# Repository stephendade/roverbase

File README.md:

# roverbase
A PCB design for Power and Motor control for small robots

This is a PCB design for a robot. It uses 4x 18650 batteries to provide a regulated power supply for electronics, power monitoring and 2x brushed motor controllers.

Todo:
Flip JST-GH power connector
5V power reg - put components closer together
Ext switch option for power switches (W/ESD protection?)
Put power power and power connectors further from battery case
Remove fuse. Look at current limiting FET?
Better alignment of labels

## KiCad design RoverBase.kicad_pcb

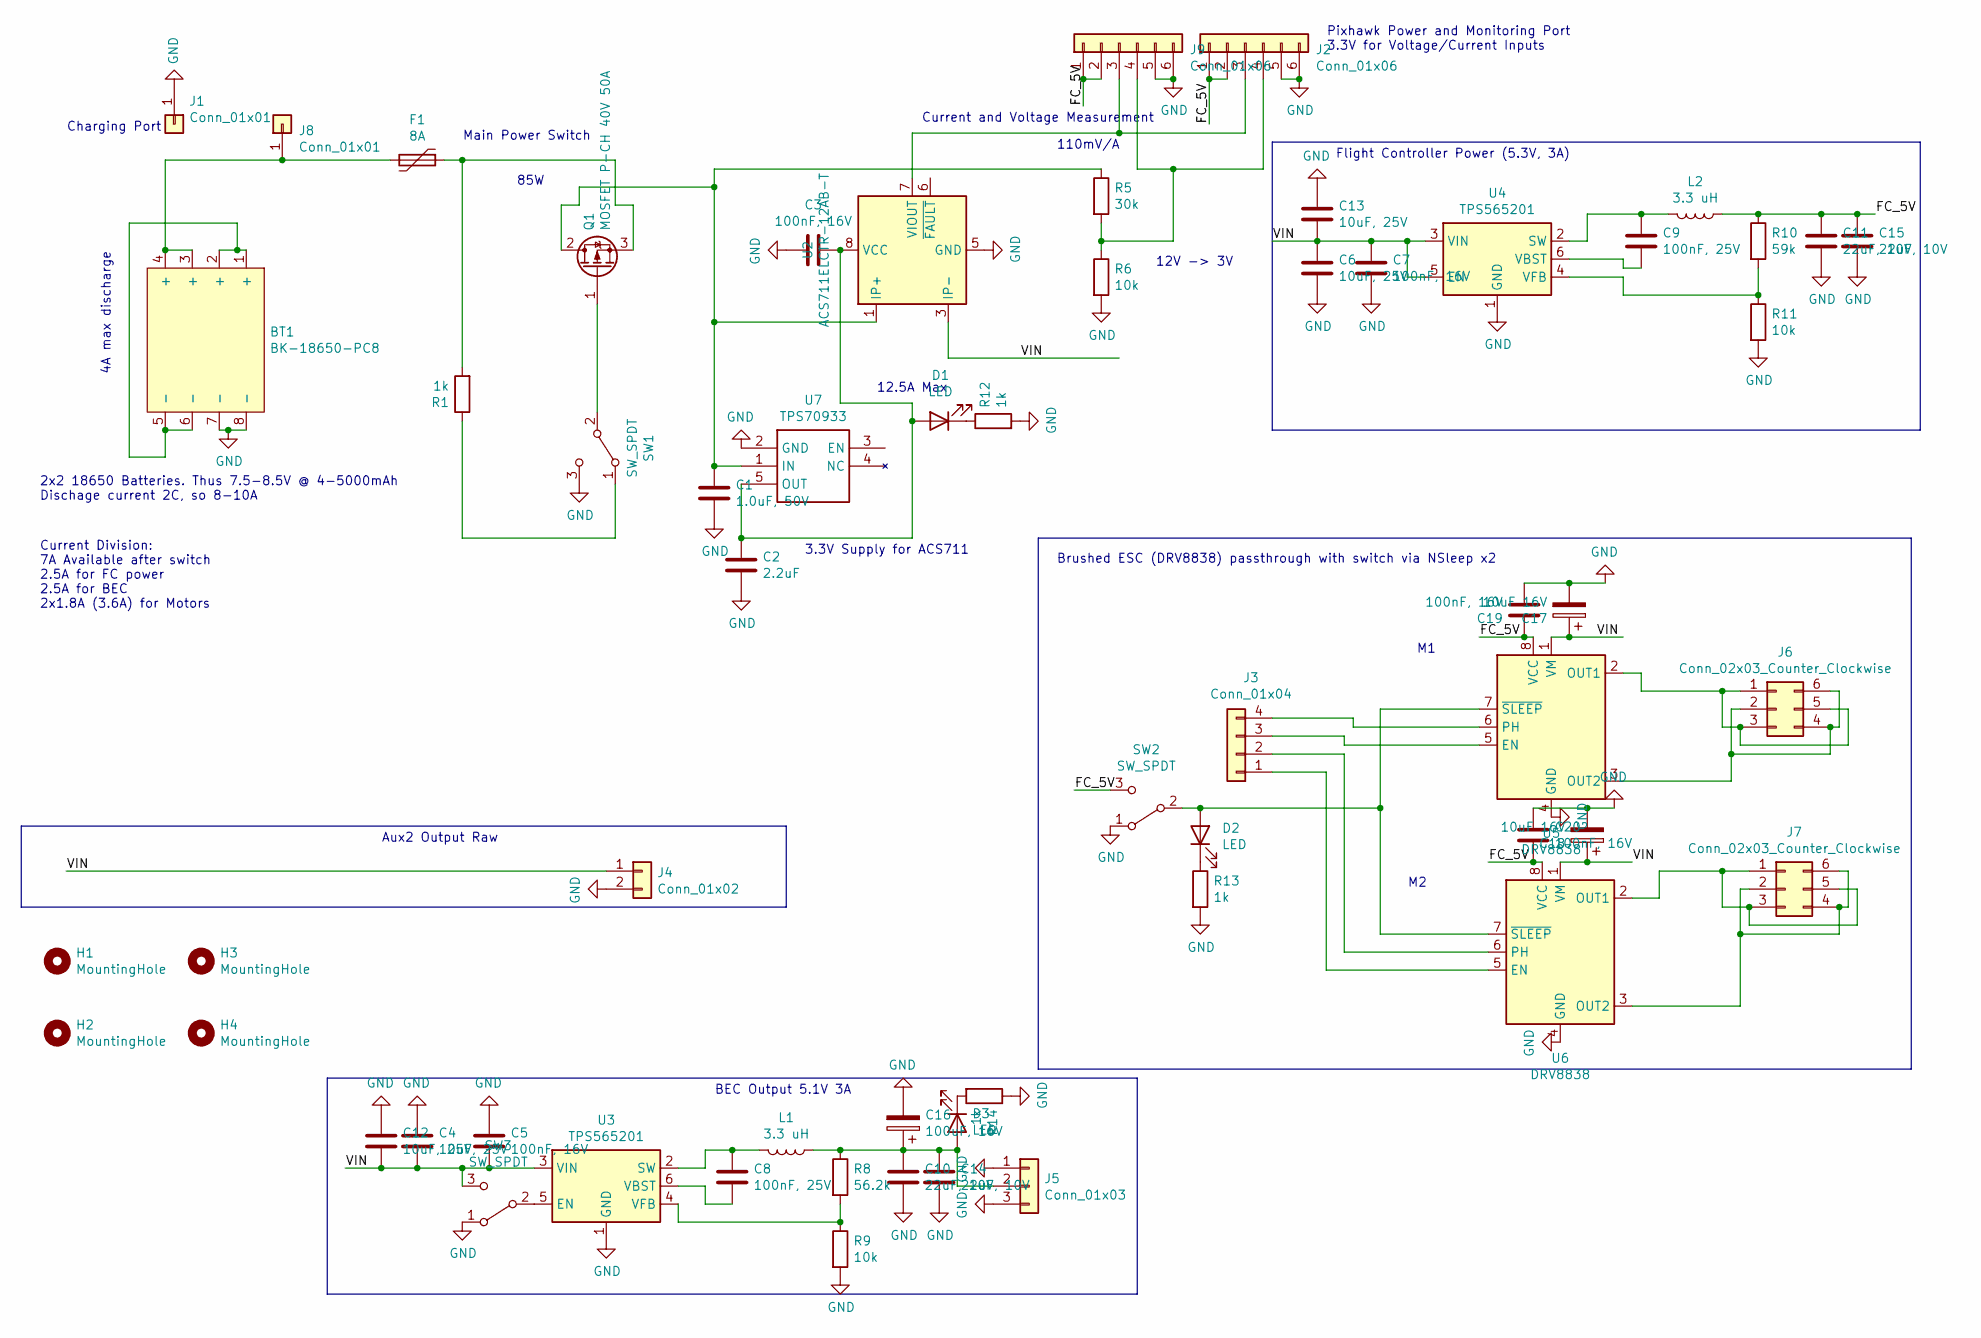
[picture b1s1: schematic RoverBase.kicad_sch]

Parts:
BT1: BK-18650-PC8; MPN BK-18650-PC8
C1: 1.0uF, 50V; C_0805_2012Metric; MPN CC0805KKX7R9BB105
C2: 2.2uF; C_0402_1005Metric; MPN GRM155R61A225KE95D
C3, C5, C7, C19, C20: 100nF, 16V; C_0402_1005Metric; MPN GRM155R71C104KA88D
C4, C6, C12, C13: 10uF, 25V; C_0805_2012Metric; MPN GRM21BR61E106MA73L
C8, C9: 100nF, 25V; C_0603_1608Metric; MPN C0603C104Z3VACTU
C10, C11, C14, C15: 22uF, 10V; C_0603_1608Metric_Pad1.08x0.95mm_HandSolder; MPN C1608X5R1A226M080AC
C16: 100uF, 16V; CP_Elec_6.3x5.4_Nichicon; MPN UWX1C101MCL1GB
C17, C18: 10uF 16V; CP_Elec_4x5.4; MPN EEE-1CA100SR
D1, D2, D3: LED; LED_0603_1608Metric; MPN LTST-C193KGKT-5A
F1: 8A; Fuse_Bourns_MF-RG800; MPN Bourns Inc.
H1, H2, H3, H4: MountingHole; MountingHole_3.5mm; MPN nf
J1, J8: Conn_01x01; Pin_D1.3mm_L11.0mm; MPN nf
J2: Conn_01x06; JST_GH_BM06B-GHS-TBT_1x06-1MP_P1.25mm_Vertical; MPN BM06B-GHS-TBT(LF)(SN)(N)
J3: Conn_01x04; PinHeader_1x04_P2.54mm_Vertical; MPN 61300411121
J4: Conn_01x02; PinHeader_1x02_P2.54mm_Vertical; MPN nf
J5: Conn_01x03; PinHeader_1x03_P2.54mm_Vertical; MPN nf
J6, J7: Conn_02x03_Counter_Clockwise; PinHeader_2x03_P2.54mm_Vertical; MPN nf
J9: Conn_01x06; PinHeader_1x06_P2.54mm_Vertical; MPN nf
L1, L2: 3.3 uH; L_Vishay_IHLP-3232; MPN IHLP3232DZER3R3M01
Q1: MOSFET P-CH 40V 50A; TO-263-2; MPN SQM40081EL_GE3
R1, R12, R13, R14: 1k; R_0402_1005Metric_Pad0.72x0.64mm_HandSolder; MPN CRCW04021K00FKEDHP
R5: 30k; R_0402_1005Metric_Pad0.72x0.64mm_HandSolder; MPN CRCW040230K0FKEDC
R6, R9, R11: 10k; R_0402_1005Metric_Pad0.72x0.64mm_HandSolder; MPN CRCW040210K0FKED
R8: 56.2k; R_0402_1005Metric_Pad0.72x0.64mm_HandSolder; MPN CRCW040256K2FKED
R10: 59k; R_0402_1005Metric_Pad0.72x0.64mm_HandSolder; MPN CRCW040259K0FKED
SW1, SW2, SW3: SW_SPDT; SW_CuK_OS102011MA1QN1_SPDT_Angled; MPN OS102011MA1QN1
U2: ACS711ELCTR-12AB-T; SOIC-8_3.9x4.9mm_P1.27mm; MPN ACS711ELCTR-12AB-T
U3, U4: TPS565201; SOT-23-6; MPN TPS565201DDCR
U5, U6: DRV8838; WSON-8-1EP_2x2mm_P0.5mm_EP0.9x1.6mm_ThermalVias; MPN DRV8838DSGR
U7: TPS70933; SOT-23-5_HandSoldering; MPN TPS70933DBVT

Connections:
/FC_5V: C11.1, C15.1, C19.1, C20.2, J2.1, J2.2, J9.1, J9.2, L2.1, R10.1, SW2.3 (C), U5.8 (VCC), U6.8 (VCC)
/VIN: C4.2, C5.2, C6.1, C7.1, C12.2, C13.2, C17.1, C18.1, J4.1, SW3.3 (C), U2.3 (IP-), U2.4 (IP-), U3.3 (VIN), U4.3 (VIN), U4.5 (EN), U5.1 (VM), U6.1 (VM)
GND: BT1.7 (-), BT1.8 (-), C1.2, C2.2, C3.2, C4.1, C5.1, C6.2, C7.2, C10.2, C11.2, C12.1, C13.1, C14.2, C15.2, C16.2, C17.2, C18.2, C19.2, C20.1, J1.1, J2.5, J2.6, J4.2, J5.1, J5.3, J9.5, J9.6, R6.2, R9.2, R11.2, R12.2, R13.2, R14.1, SW1.3 (C), SW2.1 (A), SW3.1 (A), U2.5 (GND), U3.1 (GND), U4.1 (GND), U5.4 (GND), U5.9 (GND), U6.4 (GND), U6.9 (GND), U7.2 (GND)
unnamed: BT1.1 (+), BT1.2 (+), BT1.5 (-), BT1.6 (-)
unnamed: BT1.3 (+), BT1.4 (+), F1.2, J8.1
unnamed: C1.1, Q1.2 (D), R5.1, U2.1 (IP+), U2.2 (IP+), U7.1 (IN)
unnamed: C2.1, C3.1, D1.2 (A), U2.8 (VCC), U7.5 (OUT)
unnamed: C8.1, L1.2, U3.2 (SW)
unnamed: C8.2, U3.6 (VBST)
unnamed: C9.1, L2.2, U4.2 (SW)
unnamed: C9.2, U4.6 (VBST)
unnamed: C10.1, C14.1, C16.1, D3.2 (A), J5.2, L1.1, R8.1
unnamed: D1.1 (K), R12.1
unnamed: D2.1 (K), R13.1
unnamed: D2.2 (A), SW2.2 (B), U5.7 (~SLEEP), U6.7 (~SLEEP)
unnamed: D3.1 (K), R14.2
unnamed: F1.1, Q1.3 (S), R1.2
unnamed: J2.3, J9.3, U2.7 (VIOUT)
unnamed: J2.4, J9.4, R5.2, R6.1
unnamed: J3.1, U6.5 (EN)
unnamed: J3.2, U6.6 (PH)
unnamed: J3.3, U5.5 (EN)
unnamed: J3.4, U5.6 (PH)
unnamed: J6.1, J6.3, J6.5, U5.2 (OUT1)
unnamed: J6.2, J6.4, J6.6, U5.3 (OUT2)
unnamed: J7.1, J7.3, J7.5, U6.2 (OUT1)
unnamed: J7.2, J7.4, J7.6, U6.3 (OUT2)
unnamed: Q1.1 (G), SW1.2 (B)
unnamed: R1.1, SW1.1 (A)
unnamed: R8.2, R9.1, U3.4 (VFB)
unnamed: R10.2, R11.1, U4.4 (VFB)
unnamed: SW3.2 (B), U3.5 (EN)

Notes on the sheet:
Pixhawk Power and Monitoring Port 3.3V for Voltage/Current Inputs
Aux2 Output Raw
85W
Charging Port
4A max discharge
Main Power Switch
3.3V Supply for ACS711
BEC Output 5.1V 3A
2x2 18650 Batteries. Thus 7.5-8.5V @ 4-5000mAh Dischage current 2C, so 8-10A
Flight Controller Power (5.3V, 3A)
12V -> 3V
Current Division: 7A Available after switch 2.5A for FC power 2.5A for BEC 2x1.8A (3.6A) for Motors
12.5A Max
Brushed ESC (DRV8838) passthrough with switch via NSleep x2
Current and Voltage Measurement
110mV/A

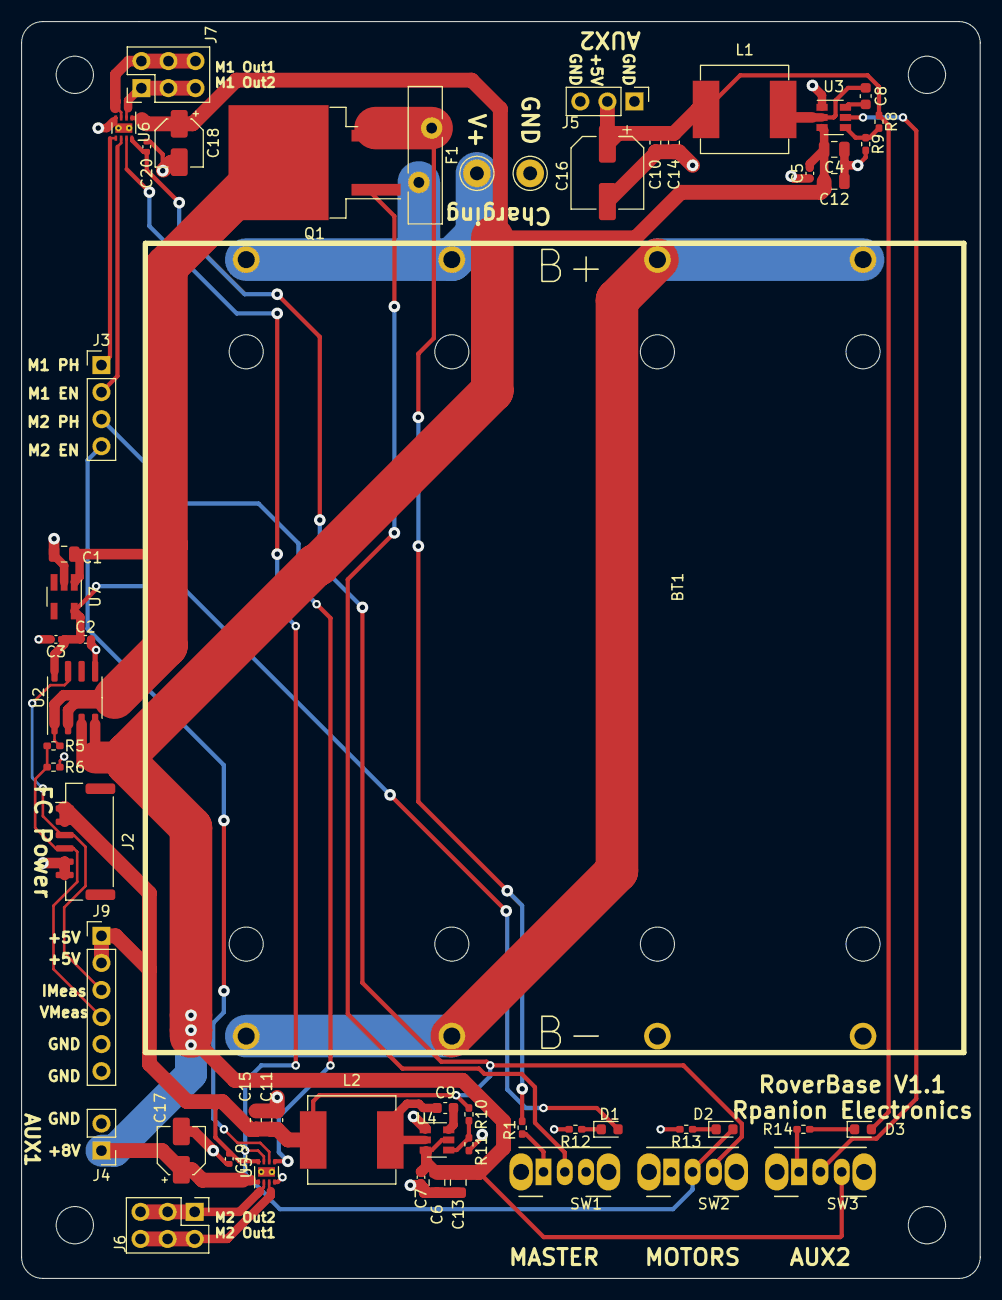
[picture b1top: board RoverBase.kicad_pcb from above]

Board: 2 copper layers, 90.0 x 118.0 mm, 60 parts (0 on the bottom side), 32 nets.

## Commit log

2021-01-07 Add GPL
2021-01-08 Fixes from V1 testing
2021-01-09 Updated inductor footprint
2021-01-09 Better power supply placement
2021-01-31 Updated motor controllers
2021-02-20 Smaller size pcb and re-layout
2021-02-23 Update board pins
2021-02-23 Added power system diagram
2021-03-01 FC Power 5.1V to 5.3V
2021-03-01 Cleanup and consolidate
2021-03-19 Remove diodes and add thermal via for motor controllers
2021-03-20 RoHS Compliance
2021-06-17 Using FET and fuse instead of switch
2021-08-24 Update RoHS compliance
2021-08-24 Minor PCB updates
2021-08-24 Remove KiBOM
2021-12-30 Upgrade to KiCad6
